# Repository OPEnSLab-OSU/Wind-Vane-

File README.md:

# Wind_Vane
Wind Sensor (Humidity/Temperature &amp; Magnetometer)

The Wind Vane is a environment sensing and logging tool. It will sense the direction of the wind and relative temperature and humidity. It will be recording data every ten senconds and storing it in a microSD. 

All the eagle designs for the PCB will be found here. They will update as soon a new version is made. 

The STL file for the casing will also be found here.

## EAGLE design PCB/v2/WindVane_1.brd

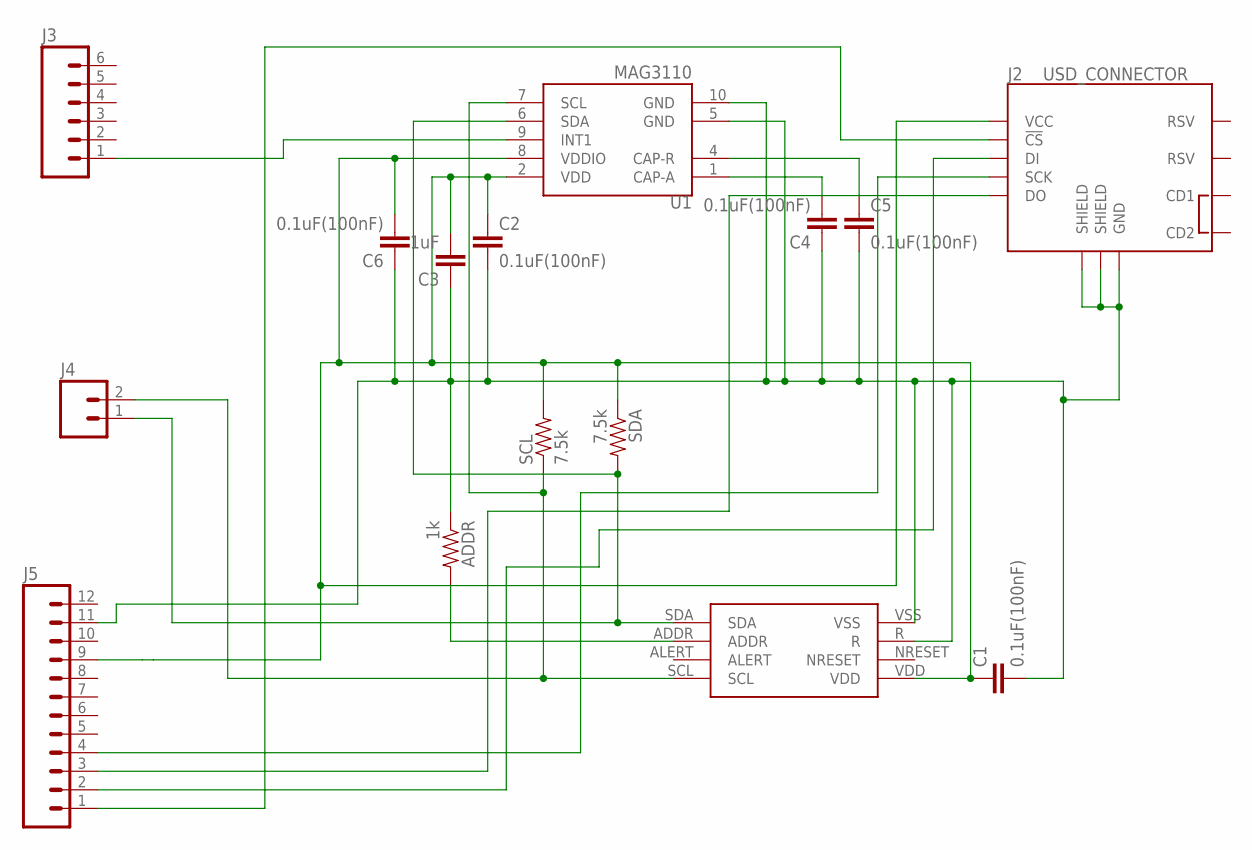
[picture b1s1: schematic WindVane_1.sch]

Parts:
ADDR: 1k; 1206
C1, C2, C4, C5, C6: 0.1uF(100nF); 0603-CAP
C3: 1uF; 0402-CAP
J2: USD_CONNECTOR; MICRO-SD-SOCKET-PP
J3: M06NO_SILK_YES_STOP; 1X06_NO_SILK_YES_STOP
J4: M02PTH; 1X02
J5: M121X12_NO_SILK_KIT; 1X12_NO_SILK_KIT
SCL: 7.5k; 1206
SDA: 7.5k; 1206
U1: MAG3110; DFN-10
U$1: SHT3X-DISSURFACE_MOUNT; SHT3X-DIS

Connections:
unnamed: J4.1, SDA.2, U1.6 (SDA), U$1.SDA
unnamed: J2.DI, J5.2
unnamed: ADDR.1, C1.2, C2.2, C3.1, C4.1, C5.2, C6.1, J2.GND, J2.GND1 (SHIELD), J2.GND3 (SHIELD), J5.11, U1.5 (GND), U1.10 (GND), U$1.R, U$1.VSS
unnamed: J4.2, SCL.1, U1.7 (SCL), U$1.SCL
unnamed: ADDR.2, U$1.ADDR
unnamed: C4.2, U1.1 (CAP-A)
unnamed: J3.1, U1.9 (INT1)
unnamed: C1.1, C2.1, C3.2, C6.2, J2.VCC, J5.9, SCL.2, SDA.1, U1.2 (VDD), U1.8 (VDDIO), U$1.VDD
unnamed: C5.1, U1.4 (CAP-R)
unnamed: J2.CS (!CS), J5.1
unnamed: J2.SCLK (SCK), J5.4
unnamed: J2.DO, J5.3

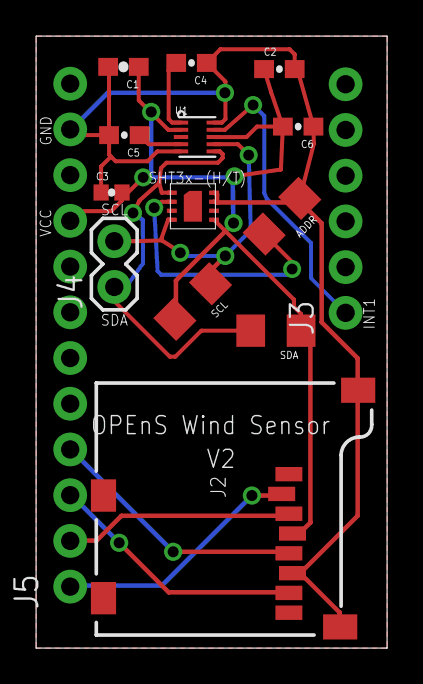
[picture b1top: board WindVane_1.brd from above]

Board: 2 copper layers, 19.5 x 34.0 mm, 15 parts (0 on the bottom side), 12 nets.

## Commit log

2016-08-08 Create placeholder
2016-09-13 Create version2
2016-09-13 Add files via upload
    Second versions of the Wind Vane PCB
2016-10-19 Create Readme-windvane

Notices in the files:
parts and their libraries:
SparkFun-Passives: Licensing: Creative Commons ShareAlike 4.0 International - https://creativecommons.org/licenses/by-sa/4.0
